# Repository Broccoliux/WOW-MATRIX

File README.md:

# WOW MATRIX
8x8x8 LED 3D Matrix

Built by Broccoli > ME <

## what this project is

This project is my WiFi controlled 8x8x8 LED cube thing and honestly it is kinda fire

The app folder is the browser controller and the frimware folder is the ESP32 S3 code and the tiny local web server running on the board

The 3D enclosure is done and the PCB is done too the only part missing on the enclosure is the LED mounts because I am gonna add those once I print the enclosure and test the fit

The main thing still missing right now is the firmware because that is the part that actually makes the cube run for real

## repo layout

```text
WOW MATRIX/
    app/
        index html       browser UI
        script js        3D cube logic controls animations WiFi sending
        style css        page styling and LED visuals
        firmware/        another firmware folder that exists in the app area
    frimware/
        platformio ini   ESP32 S3 PlatformIO config
        src/             ESP32 source files
        data/            files served by the ESP32 web server
    CAD/               cube design files and mechanical work
    imgs/              project images
    Matrix/            KiCad project and PCB related files
```

The real firmware folder is the root frimware not app firmware and that is the one that matters for flashing and deployment

## how the web app works

The browser creates 512 LED objects in JavaScript Each LED has

```text
x = 0 to 7
y = 0 to 7
z = 0 to 7
color = RGB
```

The data is stored in this order

```text
index = z * 64 + y * 8 + x
```

This is basically a visual 3D model of the cube CSS 3D transforms place each LED dot in space and dragging the viewport rotates the whole cube around X Y and Z The LEDs are rendered as little glowing bulbs with a highlight a colored center and a dark socket behind them

## controls in the page

### bulk selection

Use the LED table checkboxes to pick a bunch of voxels choose a color and hit Apply That updates the browser model and sends the frame to the ESP32 when the cube is connected

### animations

The current animation lineup is

- Rain drops fall down the Y axis in every X Z column
- Pulse the whole cube brightens and dims with the selected animation color
- Wave brightness moves through X Y and Z together
- Bouncing Ball a bright ball travels through the cube volume
- Lightning a quick flash path jumps through multiple voxels

The animation color picker is separate from the bulk selection color because changing the bulk color should not silently change the animation color That would be weird and annoying also some animations are still a little rough and I will clean them up later

### image mapper

Use the Image Mapper to load a photo or image The browser draws it into an 8x8 canvas and reads the pixels with Canvas getImageData

There are two modes

- 3D Volume each image pixel is copied across all 8 Z layers so a full 8x8 image can use all 512 LEDs
- Front Face each image pixel only appears on the front face so it uses up to 64 LEDs

Super dark or transparent pixels stay off The original RGB values are preserved per LED so the image does not get flattened into one single color

Loading an image also stops the current animation because the image frame has to stay on the cube

## ESP32 WiFi setup

The ESP32 S3 starts its own WiFi network not the home router Very on brand for a tiny cube project

```text
WiFi name LED_Cube_Controller
Password password123
ESP32 IP 192 168 4 1
```

The ESP32 also runs a DNS server If you type a hostname while connected to the cube WiFi it gets redirected to the board which is how the captive portal works on a lot of phones

If your phone does not auto open the controller just open this manually

```text
http://192 168 4 1
```

Some phones say the WiFi has no internet That is normal Just choose stay connected anyway The cube network is local and does not need internet for the controller to work

## how the ESP32 receives a frame

The browser sends a POST request to

```text
POST /api/frame
```

The request body is base64 text After decoding it has to contain exactly

```text
512 LEDs x 3 bytes = 1536 bytes
```

The bytes are sent in this order

```text
for z 0..7
    for y 0..7
        for x 0..7
            red green blue
```

Other API routes

```text
GET /api/status checks if the ESP32 is alive
POST /api/clear turns the stored frame off
```

The browser sends frames about 30 times per second while connected That limit is intentional so dragging the cube does not spam the ESP32 with a million requests

## upload the firmware and web page

You will need VS Code the PlatformIO extension and the ESP32 platform Open the root firmware folder

```text
F:\OneDrive\Desktop\cloned repos\WOW MATRIX\frimware
```

The board config is already in platformio ini

```ini
[env esp32 s3 devkitc 1]
platform = espressif32
board = esp32 s3 devkitc 1
framework = arduino
monitor_speed = 115200
```

First upload the files in data then upload the program

```bash
cd "F:\OneDrive\Desktop\cloned repos\WOW MATRIX\frimware"
pio run -t uploadfs
pio run -t upload
```

uploadfs pushes data index html data script js and data style css into the ESP32 LittleFS storage upload flashes the C++ firmware onto the board Both are needed

If you change anything in app copy the files into frimware data again before running uploadfs

```bash
copy "F:\OneDrive\Desktop\cloned repos\WOW MATRIX\app\index html" "F:\OneDrive\Desktop\cloned repos\WOW MATRIX\frimware\data\index html"
copy "F:\OneDrive\Desktop\cloned repos\WOW MATRIX\app\script js" "F:\OneDrive\Desktop\cloned repos\WOW MATRIX\frimware\data\script js"
copy "F:\OneDrive\Desktop\cloned repos\WOW MATRIX\app\style css" "F:\OneDrive\Desktop\cloned repos\WOW MATRIX\frimware\data\style css"
```

## what is done

The 3D enclosure is done and the PCB is done

The enclosure is missing the LED mounts for now because I am going to add those once I print the enclosure and test the fit

The main thing that is still missing is the firmware because that is the part that actually makes the cube do stuff in real life

## current status

What is working right now

- 3D 512 LED browser model
- mouse and touch rotation
- individual LED selection
- bulk color selection
- rain pulse wave ball and lightning animations
- custom animation color
- local image loading and 8x8 pixel sampling
- 3D volume image mode
- ESP32 access point setup
- captive portal routes
- status frame and clear HTTP API
- LittleFS web app serving

What is still missing

- final firmware logic to drive the real cube
- testing the real cube frame order against the physical wiring
- LED mounts on the enclosure after the print test

## final vibe

This project is made by Broccoli and that is the real energy

The software side is already pretty solid and the hardware side is basically in place now The 3D enclosure and PCB are done The only real big gap left is the firmware and that is where the focus needs to be next

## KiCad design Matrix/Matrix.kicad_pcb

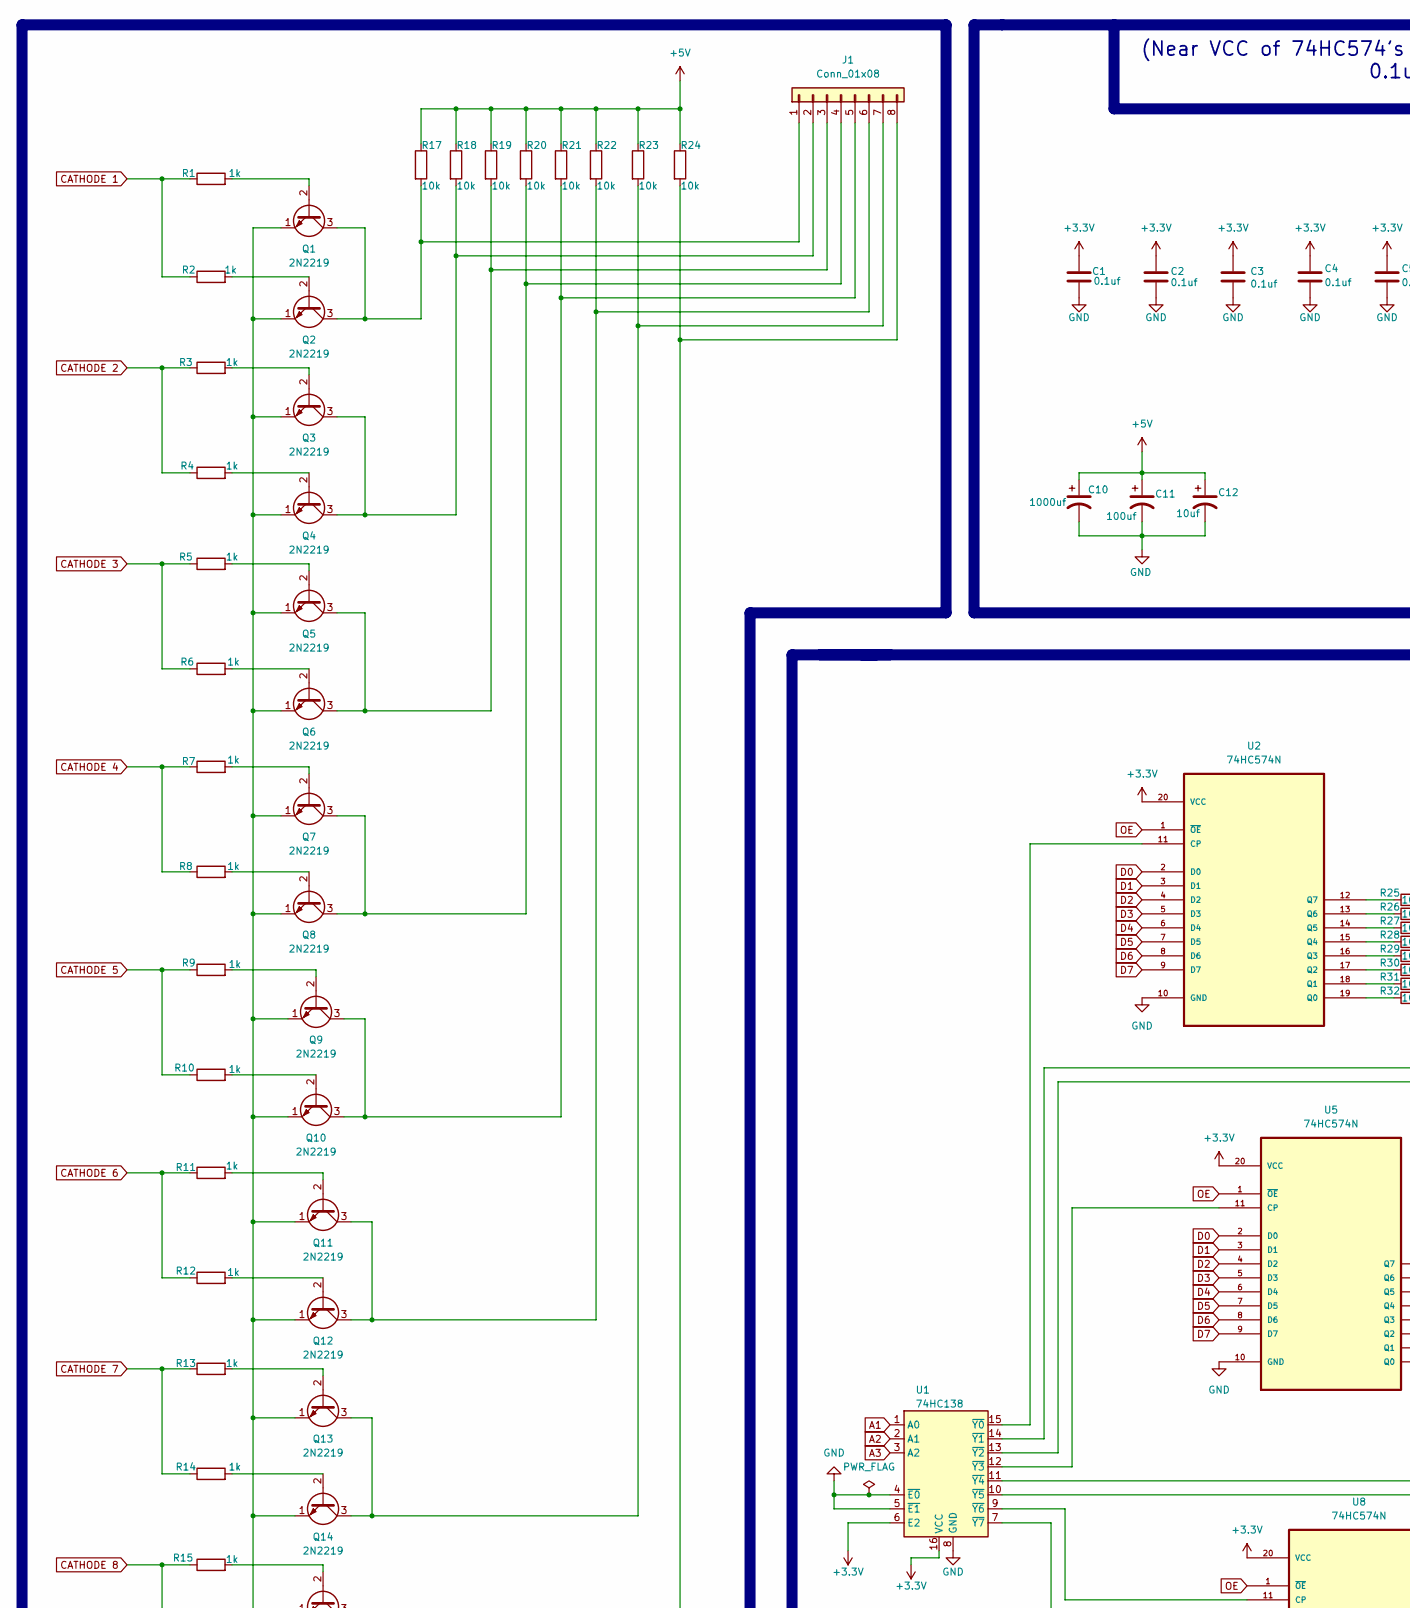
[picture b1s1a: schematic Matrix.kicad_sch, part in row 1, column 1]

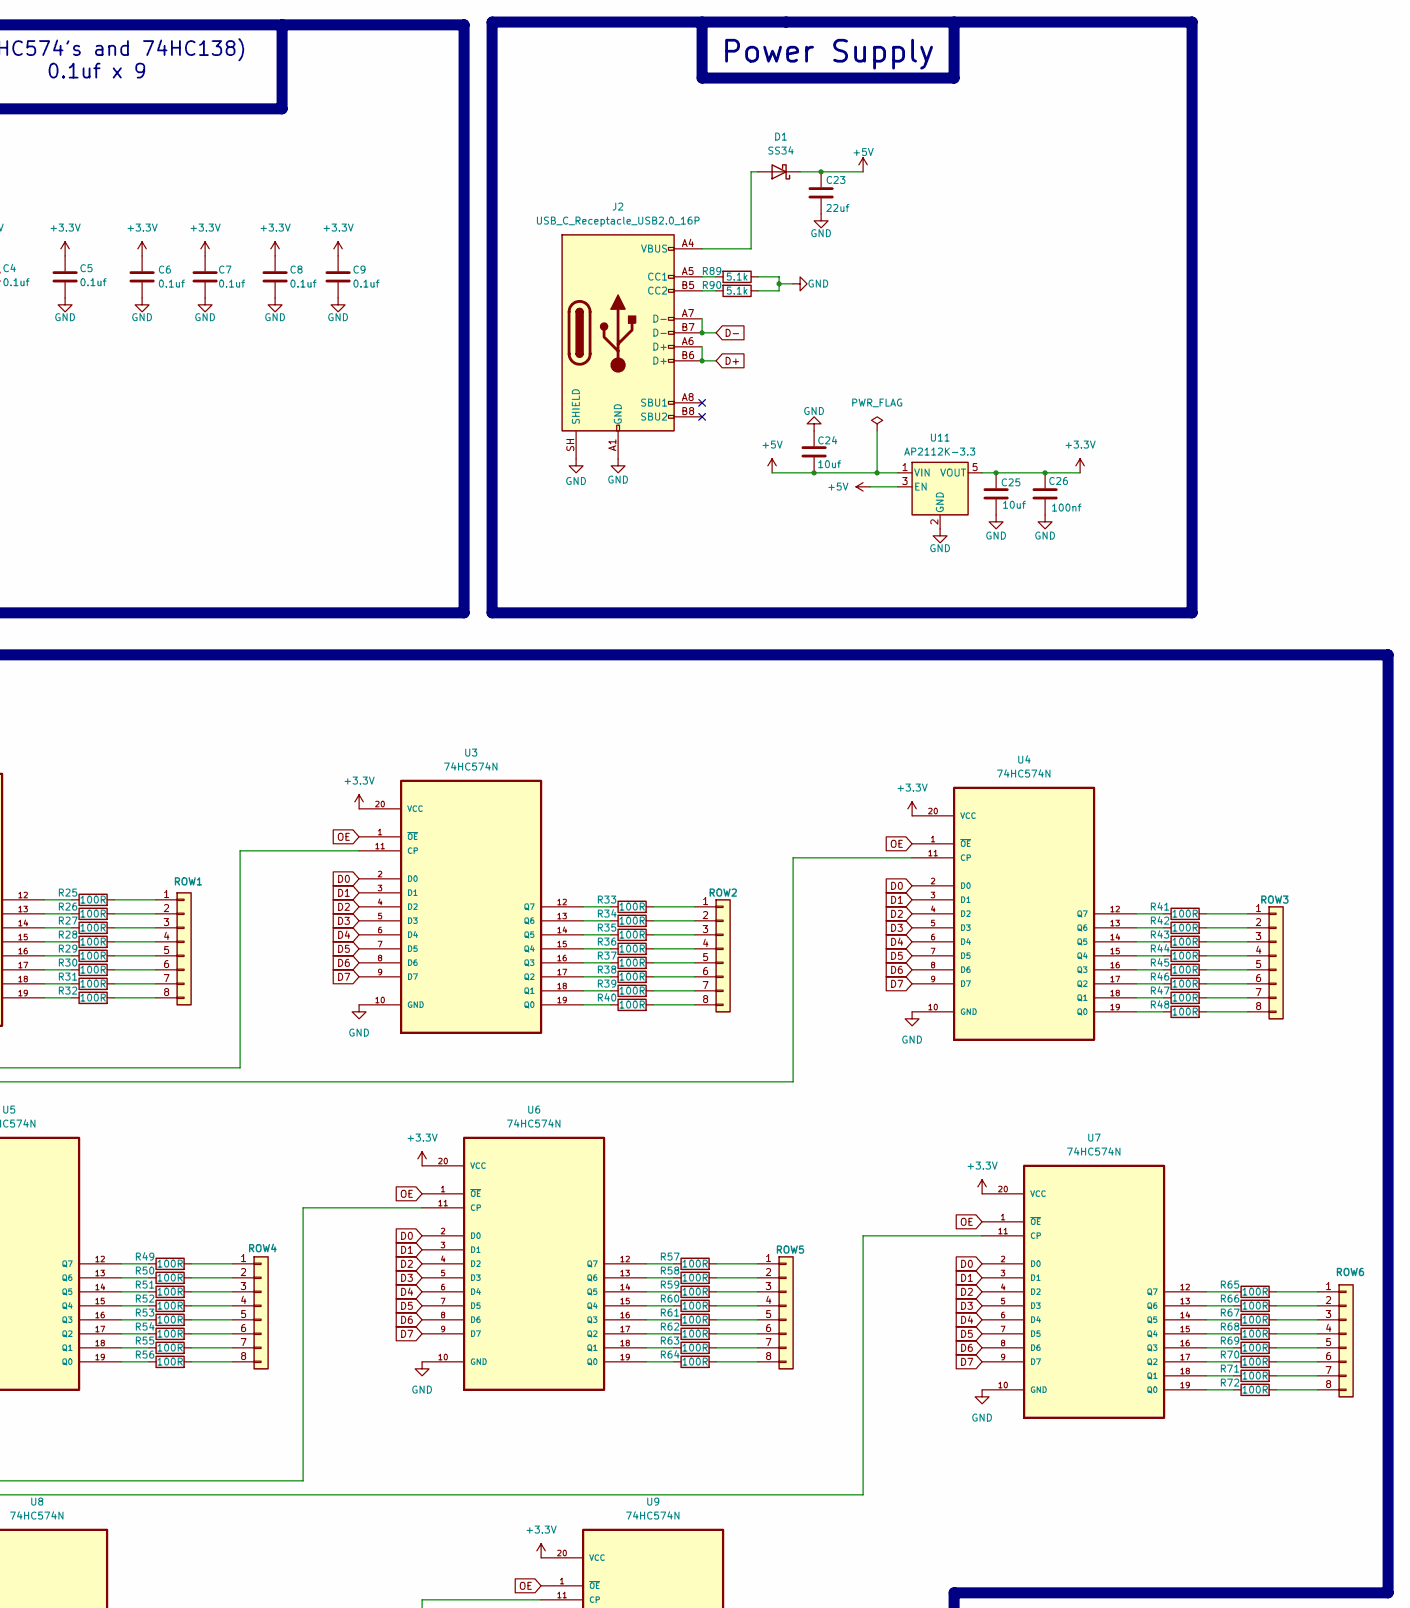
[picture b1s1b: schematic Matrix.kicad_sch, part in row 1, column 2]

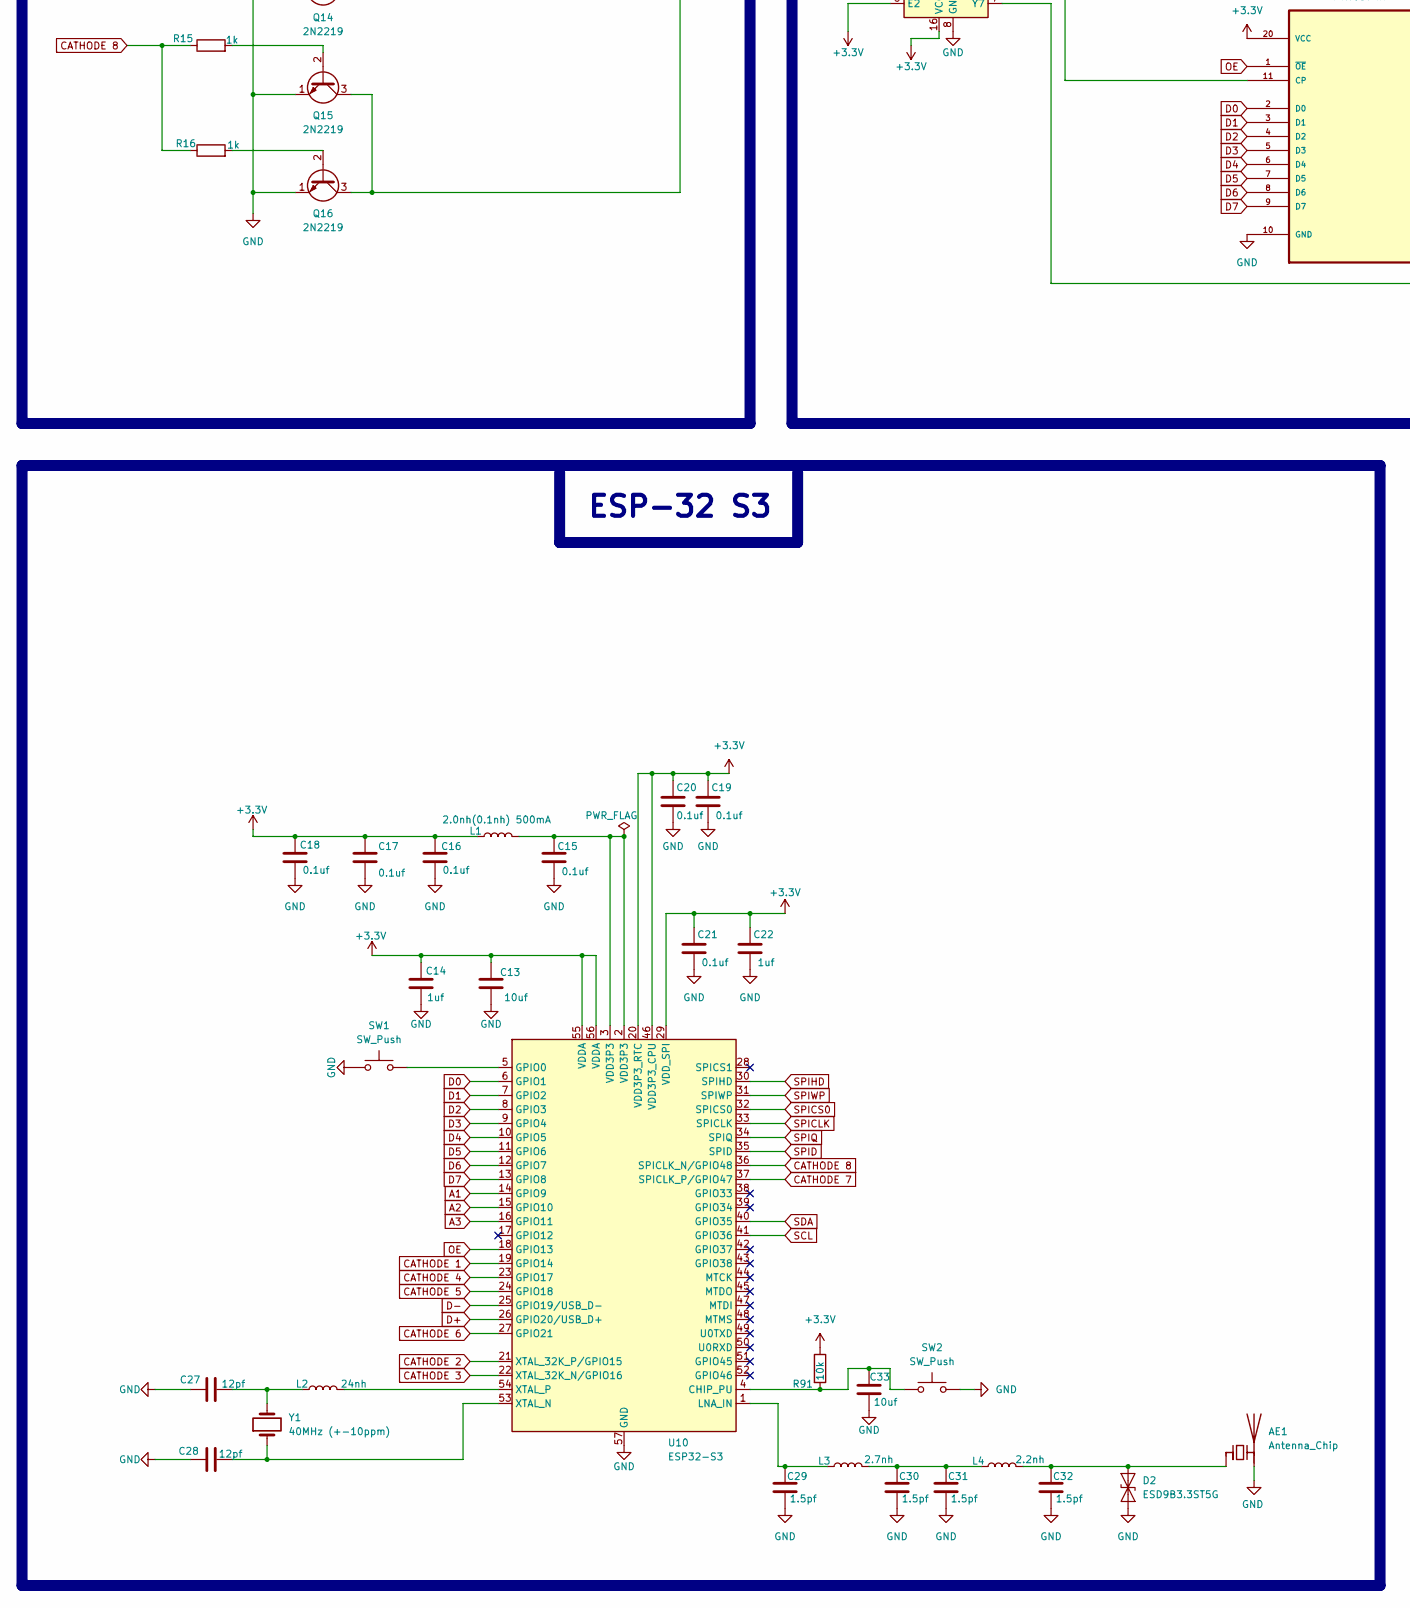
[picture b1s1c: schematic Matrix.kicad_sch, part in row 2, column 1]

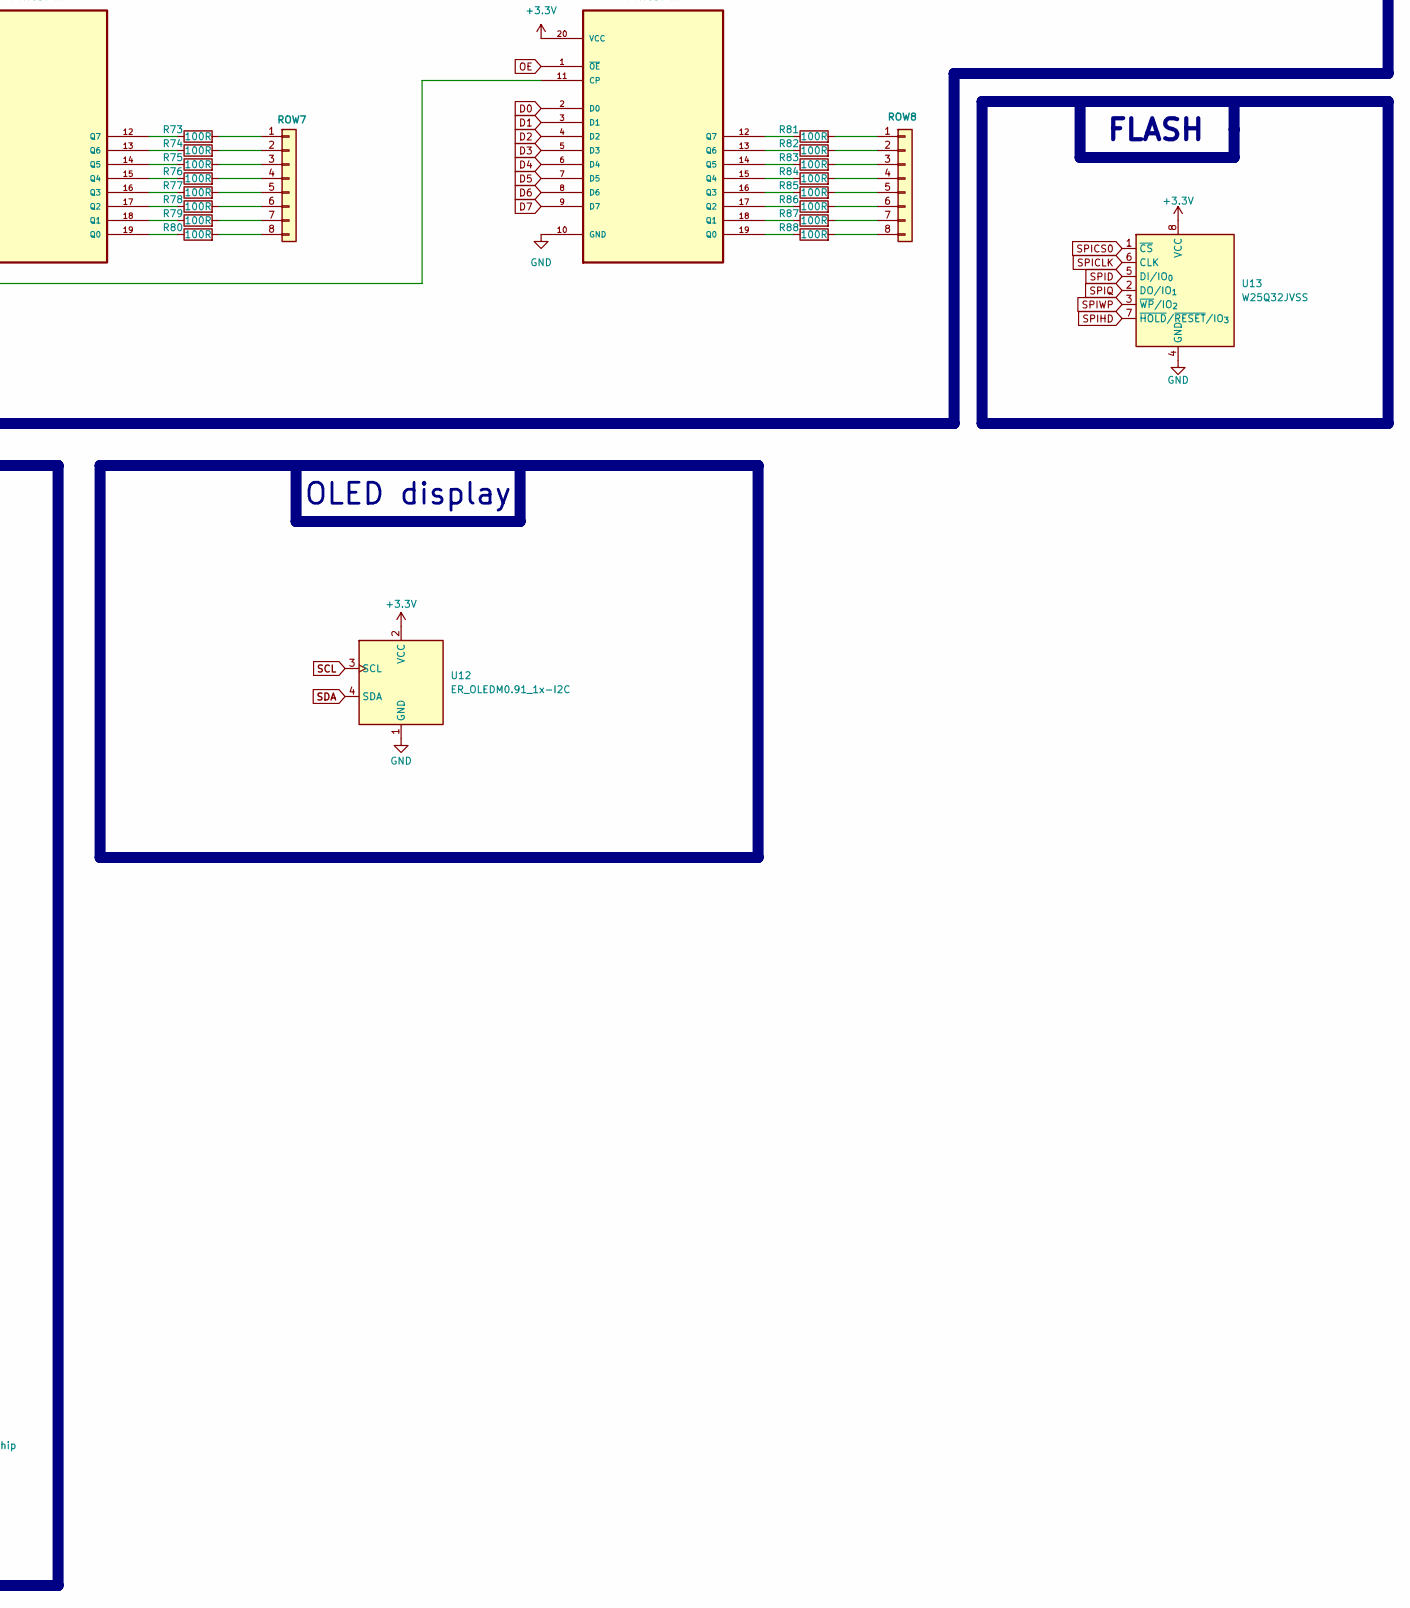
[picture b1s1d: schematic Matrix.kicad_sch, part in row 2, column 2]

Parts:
AE1: Antenna_Chip; ANTC3216X60N
C1, C2, C3, C4, C5, C6, C7, C8, C9: 0.1uf; C_0805_2012Metric
C10: 1000uf; CP_Radial_D4.0mm_P1.50mm
C11: 100uf; C_0805_2012Metric_Pad1.18x1.45mm_HandSolder
C12, C13, C24, C25, C33: 10uf; C_0805_2012Metric_Pad1.18x1.45mm_HandSolder
C14, C22: 1uf; C_0805_2012Metric_Pad1.18x1.45mm_HandSolder
C15, C16, C17, C18, C19, C20, C21: 0.1uf; C_0805_2012Metric_Pad1.18x1.45mm_HandSolder
C23: 22uf; C_0805_2012Metric_Pad1.18x1.45mm_HandSolder
C26: 100nf; C_0805_2012Metric_Pad1.18x1.45mm_HandSolder
C27, C28: 12pf; C_0805_2012Metric_Pad1.18x1.45mm_HandSolder
C29, C30, C31, C32: 1.5pf; C_0805_2012Metric_Pad1.18x1.45mm_HandSolder
D1: SS34; D_SMA
D2: ESD9B3.3ST5G; D_SOD-923
J1: Conn_01x08; PinHeader_1x08_P1.00mm_Vertical
J2: USB_C_Receptacle_USB2.0_16P; USB_C_Receptacle_GCT_USB4105-xx-A_16P_TopMnt_Horizontal
L1: 2.0nh(0.1nh) 500mA; L_0805_2012Metric_Pad1.05x1.20mm_HandSolder
L2: 24nh; L_0805_2012Metric_Pad1.05x1.20mm_HandSolder
L3: 2.7nh; L_0805_2012Metric_Pad1.05x1.20mm_HandSolder
L4: 2.2nh; L_0805_2012Metric_Pad1.05x1.20mm_HandSolder
Q1, Q2, Q3, Q4, Q5, Q6, Q7, Q8, Q9, Q10, Q11, Q12, Q13, Q14, Q15, Q16: 2N2219; TO-39-3
R1, R2, R3, R4, R5, R6, R7, R8, R9, R10, R11, R12, R13, R14, R15, R16: 1k; R_0805_2012Metric_Pad1.20x1.40mm_HandSolder
R17, R18, R19, R20, R21, R22, R23, R24, R91: 10k; R_0805_2012Metric_Pad1.20x1.40mm_HandSolder
R25, R26, R27, R28, R29, R30, R31, R32, R33, R34, R35, R36, R37, R38, R39, R40, R41, R42, R43, R44, R45, R46, R47, R48, R49, R50, R51, R52, R53, R54, R55, R56, R57, R58, R59, R60, R61, R62, R63, R64, R65, R66, R67, R68, R69, R70, R71, R72, R73, R74, R75, R76, R77, R78, R79, R80, R81, R82, R83, R84, R85, R86, R87, R88: 100R; R_0805_2012Metric_Pad1.20x1.40mm_HandSolder
R89, R90: 5.1k; R_0805_2012Metric_Pad1.20x1.40mm_HandSolder
ROW1, ROW2, ROW3, ROW4, ROW5, ROW6, ROW7, ROW8: Conn_01x08; PinHeader_1x08_P1.00mm_Vertical
SW1, SW2: SW_Push; SW_SPST_PTS645Sx43SMTR92
U1: 74HC138; SOIC127P600X175-16N
U2, U3, U4, U5, U6, U7, U8, U9: 74HC574N; DIP254P762X420-20; MPN 74HC574N
U10: ESP32-S3; QFN-56-1EP_7x7mm_P0.4mm_EP4x4mm
U11: AP2112K-3.3; SOT-23-5
U12: ER_OLEDM0.91_1x-I2C
U13: W25Q32JVSS; SOIC-8_5.3x5.3mm_P1.27mm
Y1: 40MHz (+-10ppm); Crystal_SMD_3225-4Pin_3.2x2.5mm_HandSoldering

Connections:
+3.3V: C1.1, C2.1, C3.1, C4.1, C5.1, C6.1, C7.1, C8.1, C9.1, C13.1, C14.1, C16.1, C17.1, C18.1, C19.1, C20.1, C21.1, C22.1, C25.1, C26.1, L1.1, R91.1, U1.6 (E2), U1.16 (VCC), U2.20 (VCC), U3.20 (VCC), U4.20 (VCC), U5.20 (VCC), U6.20 (VCC), U7.20 (VCC), U8.20 (VCC), U9.20 (VCC), U10.20 (VDD3P3_RTC), U10.29 (VDD_SPI), U10.46 (VDD3P3_CPU), U10.55 (VDDA), U10.56 (VDDA), U11.5 (VOUT), U12.2 (VCC), U13.8 (VCC)
+5V: C10.1, C11.1, C12.1, C23.1, C24.2, D1.1 (K), R17.1, R18.1, R19.1, R20.1, R21.1, R22.1, R23.1, R24.1, U11.1 (VIN), U11.3 (EN)
A1: U1.1 (A0), U10.14 (GPIO9)
A2: U1.2 (A1), U10.15 (GPIO10)
A3: U1.3 (A2), U10.16 (GPIO11)
CATHODE 1: R1.1, R2.1, U10.19 (GPIO14)
CATHODE 2: R3.1, R4.1, U10.21 (XTAL_32K_P/GPIO15)
CATHODE 3: R5.1, R6.1, U10.22 (XTAL_32K_N/GPIO16)
CATHODE 4: R7.1, R8.1, U10.23 (GPIO17)
CATHODE 5: R9.1, R10.1, U10.24 (GPIO18)
CATHODE 6: R11.1, R12.1, U10.27 (GPIO21)
CATHODE 7: R13.1, R14.1, U10.37 (SPICLK_P/GPIO47)
CATHODE 8: R15.1, R16.1, U10.36 (SPICLK_N/GPIO48)
D0: U2.2 (D0), U3.2 (D0), U4.2 (D0), U5.2 (D0), U6.2 (D0), U7.2 (D0), U8.2 (D0), U9.2 (D0), U10.6 (GPIO1)
D1: U2.3 (D1), U3.3 (D1), U4.3 (D1), U5.3 (D1), U6.3 (D1), U7.3 (D1), U8.3 (D1), U9.3 (D1), U10.7 (GPIO2)
D2: U2.4 (D2), U3.4 (D2), U4.4 (D2), U5.4 (D2), U6.4 (D2), U7.4 (D2), U8.4 (D2), U9.4 (D2), U10.8 (GPIO3)
D3: U2.5 (D3), U3.5 (D3), U4.5 (D3), U5.5 (D3), U6.5 (D3), U7.5 (D3), U8.5 (D3), U9.5 (D3), U10.9 (GPIO4)
D4: U2.6 (D4), U3.6 (D4), U4.6 (D4), U5.6 (D4), U6.6 (D4), U7.6 (D4), U8.6 (D4), U9.6 (D4), U10.10 (GPIO5)
D5: U2.7 (D5), U3.7 (D5), U4.7 (D5), U5.7 (D5), U6.7 (D5), U7.7 (D5), U8.7 (D5), U9.7 (D5), U10.11 (GPIO6)
D6: U2.8 (D6), U3.8 (D6), U4.8 (D6), U5.8 (D6), U6.8 (D6), U7.8 (D6), U8.8 (D6), U9.8 (D6), U10.12 (GPIO7)
D7: U2.9 (D7), U3.9 (D7), U4.9 (D7), U5.9 (D7), U6.9 (D7), U7.9 (D7), U8.9 (D7), U9.9 (D7), U10.13 (GPIO8)
D+: J2.A6 (D+), J2.B6 (D+), U10.26 (GPIO20/USB_D+)
D-: J2.A7 (D-), J2.B7 (D-), U10.25 (GPIO19/USB_D-)
GND: AE1.2 (PCB_Trace), C1.2, C2.2, C3.2, C4.2, C5.2, C6.2, C7.2, C8.2, C9.2, C10.2, C11.2, C12.2, C13.2, C14.2, C15.2, C16.2, C17.2, C18.2, C19.2, C20.2, C21.2, C22.2, C23.2, C24.1, C25.2, C26.2, C27.1, C28.1, C29.2, C30.2, C31.2, C32.2, C33.2, D2.1 (A1), J2.A1 (GND), J2.A12 (GND), J2.B1 (GND), J2.B12 (GND), J2.SH (SHIELD), Q1.1 (E), Q2.1 (E), Q3.1 (E), Q4.1 (E), Q5.1 (E), Q6.1 (E), Q7.1 (E), Q8.1 (E), Q9.1 (E), Q10.1 (E), Q11.1 (E), Q12.1 (E), Q13.1 (E), Q14.1 (E), Q15.1 (E), Q16.1 (E), R89.1, R90.1, SW1.1, SW2.2, U1.4 (~E0), U1.5 (~E1), U1.8 (GND), U2.10 (GND), U3.10 (GND), U4.10 (GND), U5.10 (GND), U6.10 (GND), U7.10 (GND), U8.10 (GND), U9.10 (GND), U10.57 (GND), U11.2 (GND), U12.1 (GND), U13.4 (GND)
unnamed: AE1.1 (FEED), C32.1, D2.2 (A2), L4.2
unnamed: C15.1, L1.2, U10.2 (VDD3P3), U10.3 (VDD3P3)
unnamed: C27.2, L2.1, Y1.2
unnamed: C30.1, C31.1, L3.2, L4.1
unnamed: D1.2 (A), J2.A4 (VBUS), J2.A9 (VBUS), J2.B4 (VBUS), J2.B9 (VBUS)
unnamed: J1.1, Q1.3 (C), Q2.3 (C), R17.2
unnamed: J1.2, Q3.3 (C), Q4.3 (C), R18.2
unnamed: J1.3, Q5.3 (C), Q6.3 (C), R19.2
unnamed: J1.4, Q7.3 (C), Q8.3 (C), R20.2
unnamed: J1.5, Q9.3 (C), Q10.3 (C), R21.2
unnamed: J1.6, Q11.3 (C), Q12.3 (C), R22.2
unnamed: J1.7, Q13.3 (C), Q14.3 (C), R23.2
unnamed: J1.8, Q15.3 (C), Q16.3 (C), R24.2
unnamed: J2.A5 (CC1), R89.2
unnamed: J2.B5 (CC2), R90.2
unnamed: Q1.2 (B), R1.2
unnamed: Q2.2 (B), R2.2
unnamed: Q3.2 (B), R3.2
unnamed: Q4.2 (B), R4.2
unnamed: Q5.2 (B), R5.2
unnamed: Q6.2 (B), R6.2
unnamed: Q7.2 (B), R7.2
unnamed: Q8.2 (B), R8.2
unnamed: Q9.2 (B), R9.2
unnamed: Q10.2 (B), R10.2
unnamed: Q11.2 (B), R11.2
unnamed: Q12.2 (B), R12.2
unnamed: Q13.2 (B), R13.2
unnamed: Q14.2 (B), R14.2
unnamed: Q15.2 (B), R15.2
unnamed: Q16.2 (B), R16.2
unnamed: R25.2, ROW1.1
unnamed: R26.2, ROW1.2
unnamed: R27.2, ROW1.3
unnamed: R28.2, ROW1.4
unnamed: R29.2, ROW1.5
unnamed: R30.2, ROW1.6
unnamed: R31.2, ROW1.7
unnamed: R32.2, ROW1.8
unnamed: R33.2, ROW2.1
unnamed: R34.2, ROW2.2
unnamed: R35.2, ROW2.3
unnamed: R36.2, ROW2.4
unnamed: R37.2, ROW2.5
unnamed: R38.2, ROW2.6
unnamed: R39.2, ROW2.7
unnamed: R40.2, ROW2.8
unnamed: R41.2, ROW3.1
unnamed: R42.2, ROW3.2
unnamed: R43.2, ROW3.3
unnamed: R44.2, ROW3.4
unnamed: R45.2, ROW3.5
unnamed: R46.2, ROW3.6
unnamed: R47.2, ROW3.7
unnamed: R48.2, ROW3.8
unnamed: R49.2, ROW4.1
unnamed: R50.2, ROW4.2
unnamed: R51.2, ROW4.3
unnamed: R52.2, ROW4.4
unnamed: R53.2, ROW4.5
unnamed: R54.2, ROW4.6
unnamed: R55.2, ROW4.7
unnamed: R56.2, ROW4.8
unnamed: R57.2, ROW5.1
unnamed: R58.2, ROW5.2
unnamed: R59.2, ROW5.3
unnamed: R60.2, ROW5.4
unnamed: R61.2, ROW5.5
unnamed: R62.2, ROW5.6
unnamed: R63.2, ROW5.7
unnamed: R64.2, ROW5.8
unnamed: R65.2, ROW6.1
unnamed: R66.2, ROW6.2
unnamed: R67.2, ROW6.3
unnamed: R68.2, ROW6.4
unnamed: R69.2, ROW6.5
unnamed: R70.2, ROW6.6
unnamed: R71.2, ROW6.7
unnamed: R72.2, ROW6.8
unnamed: R73.2, ROW7.1
unnamed: R74.2, ROW7.2
unnamed: R75.2, ROW7.3
unnamed: R76.2, ROW7.4
unnamed: R77.2, ROW7.5
unnamed: R78.2, ROW7.6
unnamed: R79.2, ROW7.7
unnamed: R80.2, ROW7.8
unnamed: R81.2, ROW8.1
unnamed: R82.2, ROW8.2
unnamed: R83.2, ROW8.3
unnamed: R84.2, ROW8.4
unnamed: R85.2, ROW8.5
unnamed: R86.2, ROW8.6
unnamed: R87.2, ROW8.7
unnamed: R88.2, ROW8.8
unnamed: U1.15 (~Y0), U2.11 (CP)
unnamed: U1.14 (~Y1), U3.11 (CP)
unnamed: U1.13 (~Y2), U4.11 (CP)
unnamed: U1.12 (~Y3), U5.11 (CP)
unnamed: U1.11 (~Y4), U6.11 (CP)
unnamed: U1.10 (~Y5), U7.11 (CP)
unnamed: U1.9 (~Y6), U8.11 (CP)
unnamed: U1.7 (~Y7), U9.11 (CP)
unnamed: R32.1, U2.19 (Q0)
unnamed: R31.1, U2.18 (Q1)
unnamed: R30.1, U2.17 (Q2)
unnamed: R29.1, U2.16 (Q3)
unnamed: R28.1, U2.15 (Q4)
unnamed: R27.1, U2.14 (Q5)
unnamed: R26.1, U2.13 (Q6)
unnamed: R25.1, U2.12 (Q7)
unnamed: R40.1, U3.19 (Q0)
unnamed: R39.1, U3.18 (Q1)
unnamed: R38.1, U3.17 (Q2)
unnamed: R37.1, U3.16 (Q3)
unnamed: R36.1, U3.15 (Q4)
unnamed: R35.1, U3.14 (Q5)
unnamed: R34.1, U3.13 (Q6)
unnamed: R33.1, U3.12 (Q7)
unnamed: R48.1, U4.19 (Q0)
unnamed: R47.1, U4.18 (Q1)
unnamed: R46.1, U4.17 (Q2)
unnamed: R45.1, U4.16 (Q3)
unnamed: R44.1, U4.15 (Q4)
unnamed: R43.1, U4.14 (Q5)
unnamed: R42.1, U4.13 (Q6)
unnamed: R41.1, U4.12 (Q7)
unnamed: R56.1, U5.19 (Q0)
unnamed: R55.1, U5.18 (Q1)
unnamed: R54.1, U5.17 (Q2)
unnamed: R53.1, U5.16 (Q3)
unnamed: R52.1, U5.15 (Q4)
unnamed: R51.1, U5.14 (Q5)
unnamed: R50.1, U5.13 (Q6)
unnamed: R49.1, U5.12 (Q7)
unnamed: R64.1, U6.19 (Q0)
unnamed: R63.1, U6.18 (Q1)
unnamed: R62.1, U6.17 (Q2)
unnamed: R61.1, U6.16 (Q3)
unnamed: R60.1, U6.15 (Q4)
unnamed: R59.1, U6.14 (Q5)
unnamed: R58.1, U6.13 (Q6)
unnamed: R57.1, U6.12 (Q7)
unnamed: R72.1, U7.19 (Q0)
unnamed: R71.1, U7.18 (Q1)
unnamed: R70.1, U7.17 (Q2)
unnamed: R69.1, U7.16 (Q3)
unnamed: R68.1, U7.15 (Q4)
unnamed: R67.1, U7.14 (Q5)
unnamed: R66.1, U7.13 (Q6)
unnamed: R65.1, U7.12 (Q7)
unnamed: R80.1, U8.19 (Q0)
unnamed: R79.1, U8.18 (Q1)
unnamed: R78.1, U8.17 (Q2)
unnamed: R77.1, U8.16 (Q3)
unnamed: R76.1, U8.15 (Q4)
unnamed: R75.1, U8.14 (Q5)
unnamed: R74.1, U8.13 (Q6)
unnamed: R73.1, U8.12 (Q7)
unnamed: R88.1, U9.19 (Q0)
unnamed: R87.1, U9.18 (Q1)
unnamed: R86.1, U9.17 (Q2)
unnamed: R85.1, U9.16 (Q3)
unnamed: R84.1, U9.15 (Q4)
unnamed: R83.1, U9.14 (Q5)
unnamed: R82.1, U9.13 (Q6)
unnamed: R81.1, U9.12 (Q7)
unnamed: C33.1, R91.2, SW2.1, U10.4 (CHIP_PU)
unnamed: SW1.2, U10.5 (GPIO0)
unnamed: C29.1, L3.1, U10.1 (LNA_IN)
unnamed: C28.2, U10.53 (XTAL_N), Y1.1
unnamed: L2.2, U10.54 (XTAL_P)
OE: U2.1 (~OE), U3.1 (~OE), U4.1 (~OE), U5.1 (~OE), U6.1 (~OE), U7.1 (~OE), U8.1 (~OE), U9.1 (~OE), U10.18 (GPIO13)
SCL: U10.41 (GPIO36), U12.3 (SCL)
SDA: U10.40 (GPIO35), U12.4 (SDA)
SPICLK: U10.33 (SPICLK), U13.6 (CLK)
SPICS0: U10.32 (SPICS0), U13.1 (~CS)
SPID: U10.35 (SPID), U13.5 (DI/IO_{0})
SPIHD: U10.30 (SPIHD), U13.7 (~HOLD/~RESET/IO_{3})
SPIQ: U10.34 (SPIQ), U13.2 (DO/IO_{1})
SPIWP: U10.31 (SPIWP), U13.3 (~WP/IO_{2})

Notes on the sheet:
(Near VCC of 74HC574's and 74HC138) 0.1uf x 9
Power Supply
FLASH
ESP-32 S3
OLED display

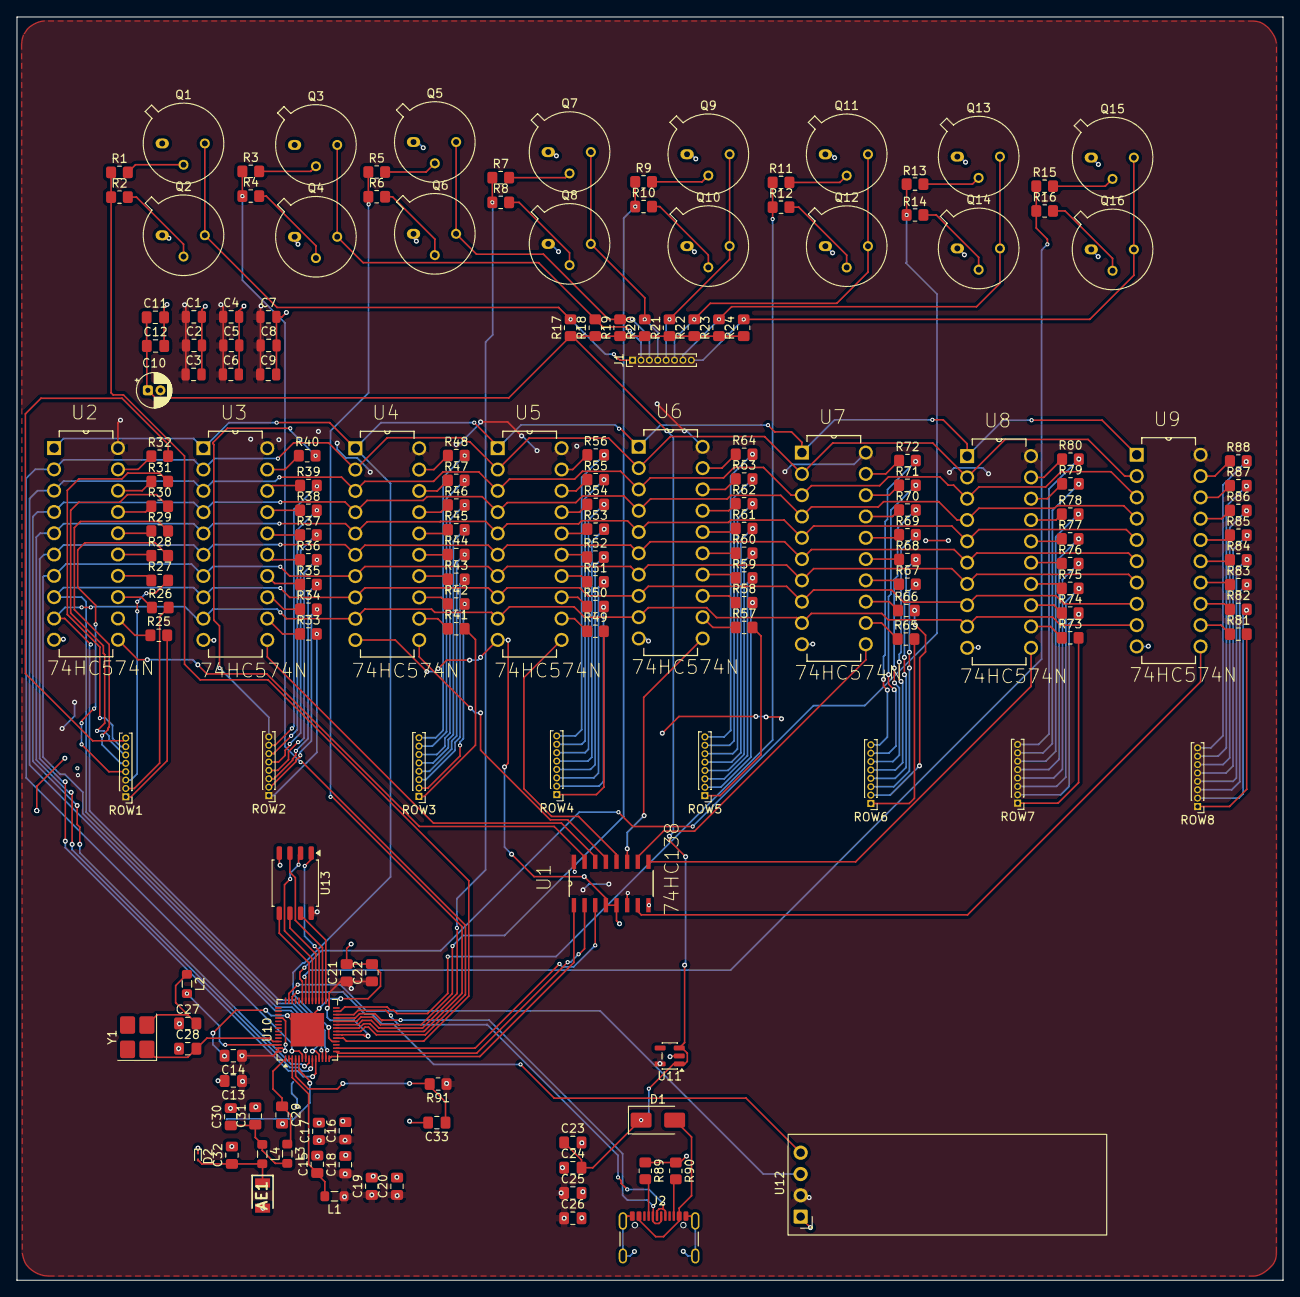
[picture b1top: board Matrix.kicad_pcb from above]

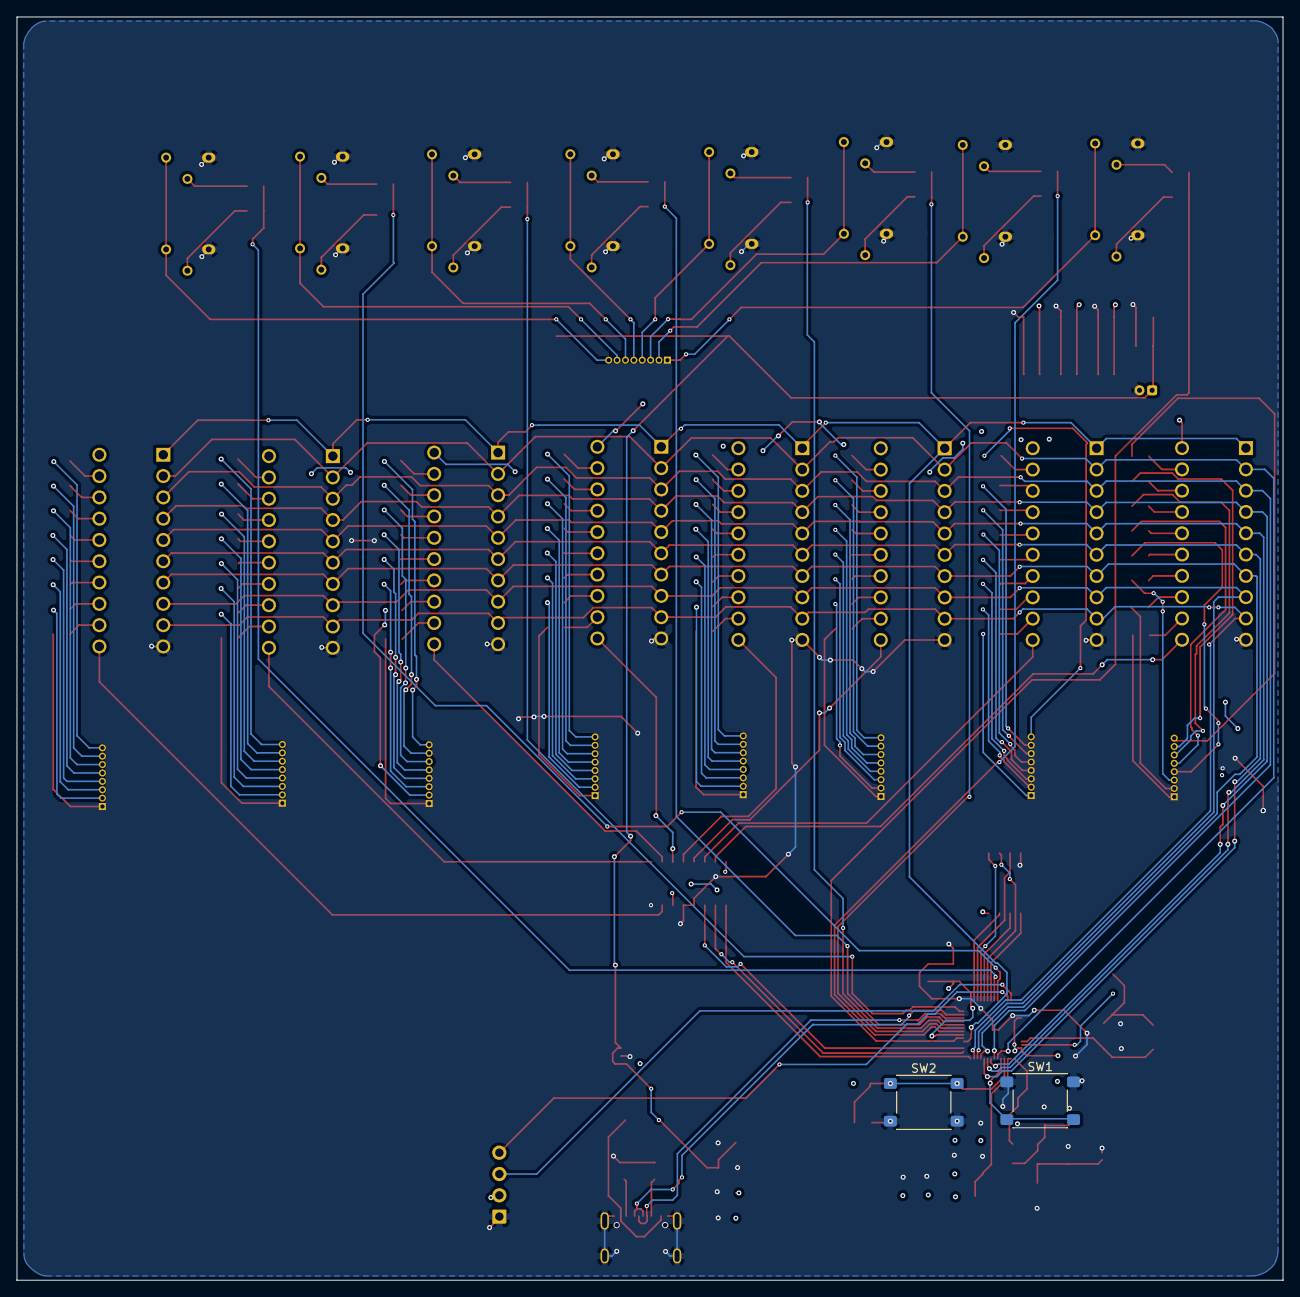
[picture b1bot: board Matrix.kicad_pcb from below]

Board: 2 copper layers, 151.0 x 150.7 mm, 173 parts (2 on the bottom side), 205 nets.
